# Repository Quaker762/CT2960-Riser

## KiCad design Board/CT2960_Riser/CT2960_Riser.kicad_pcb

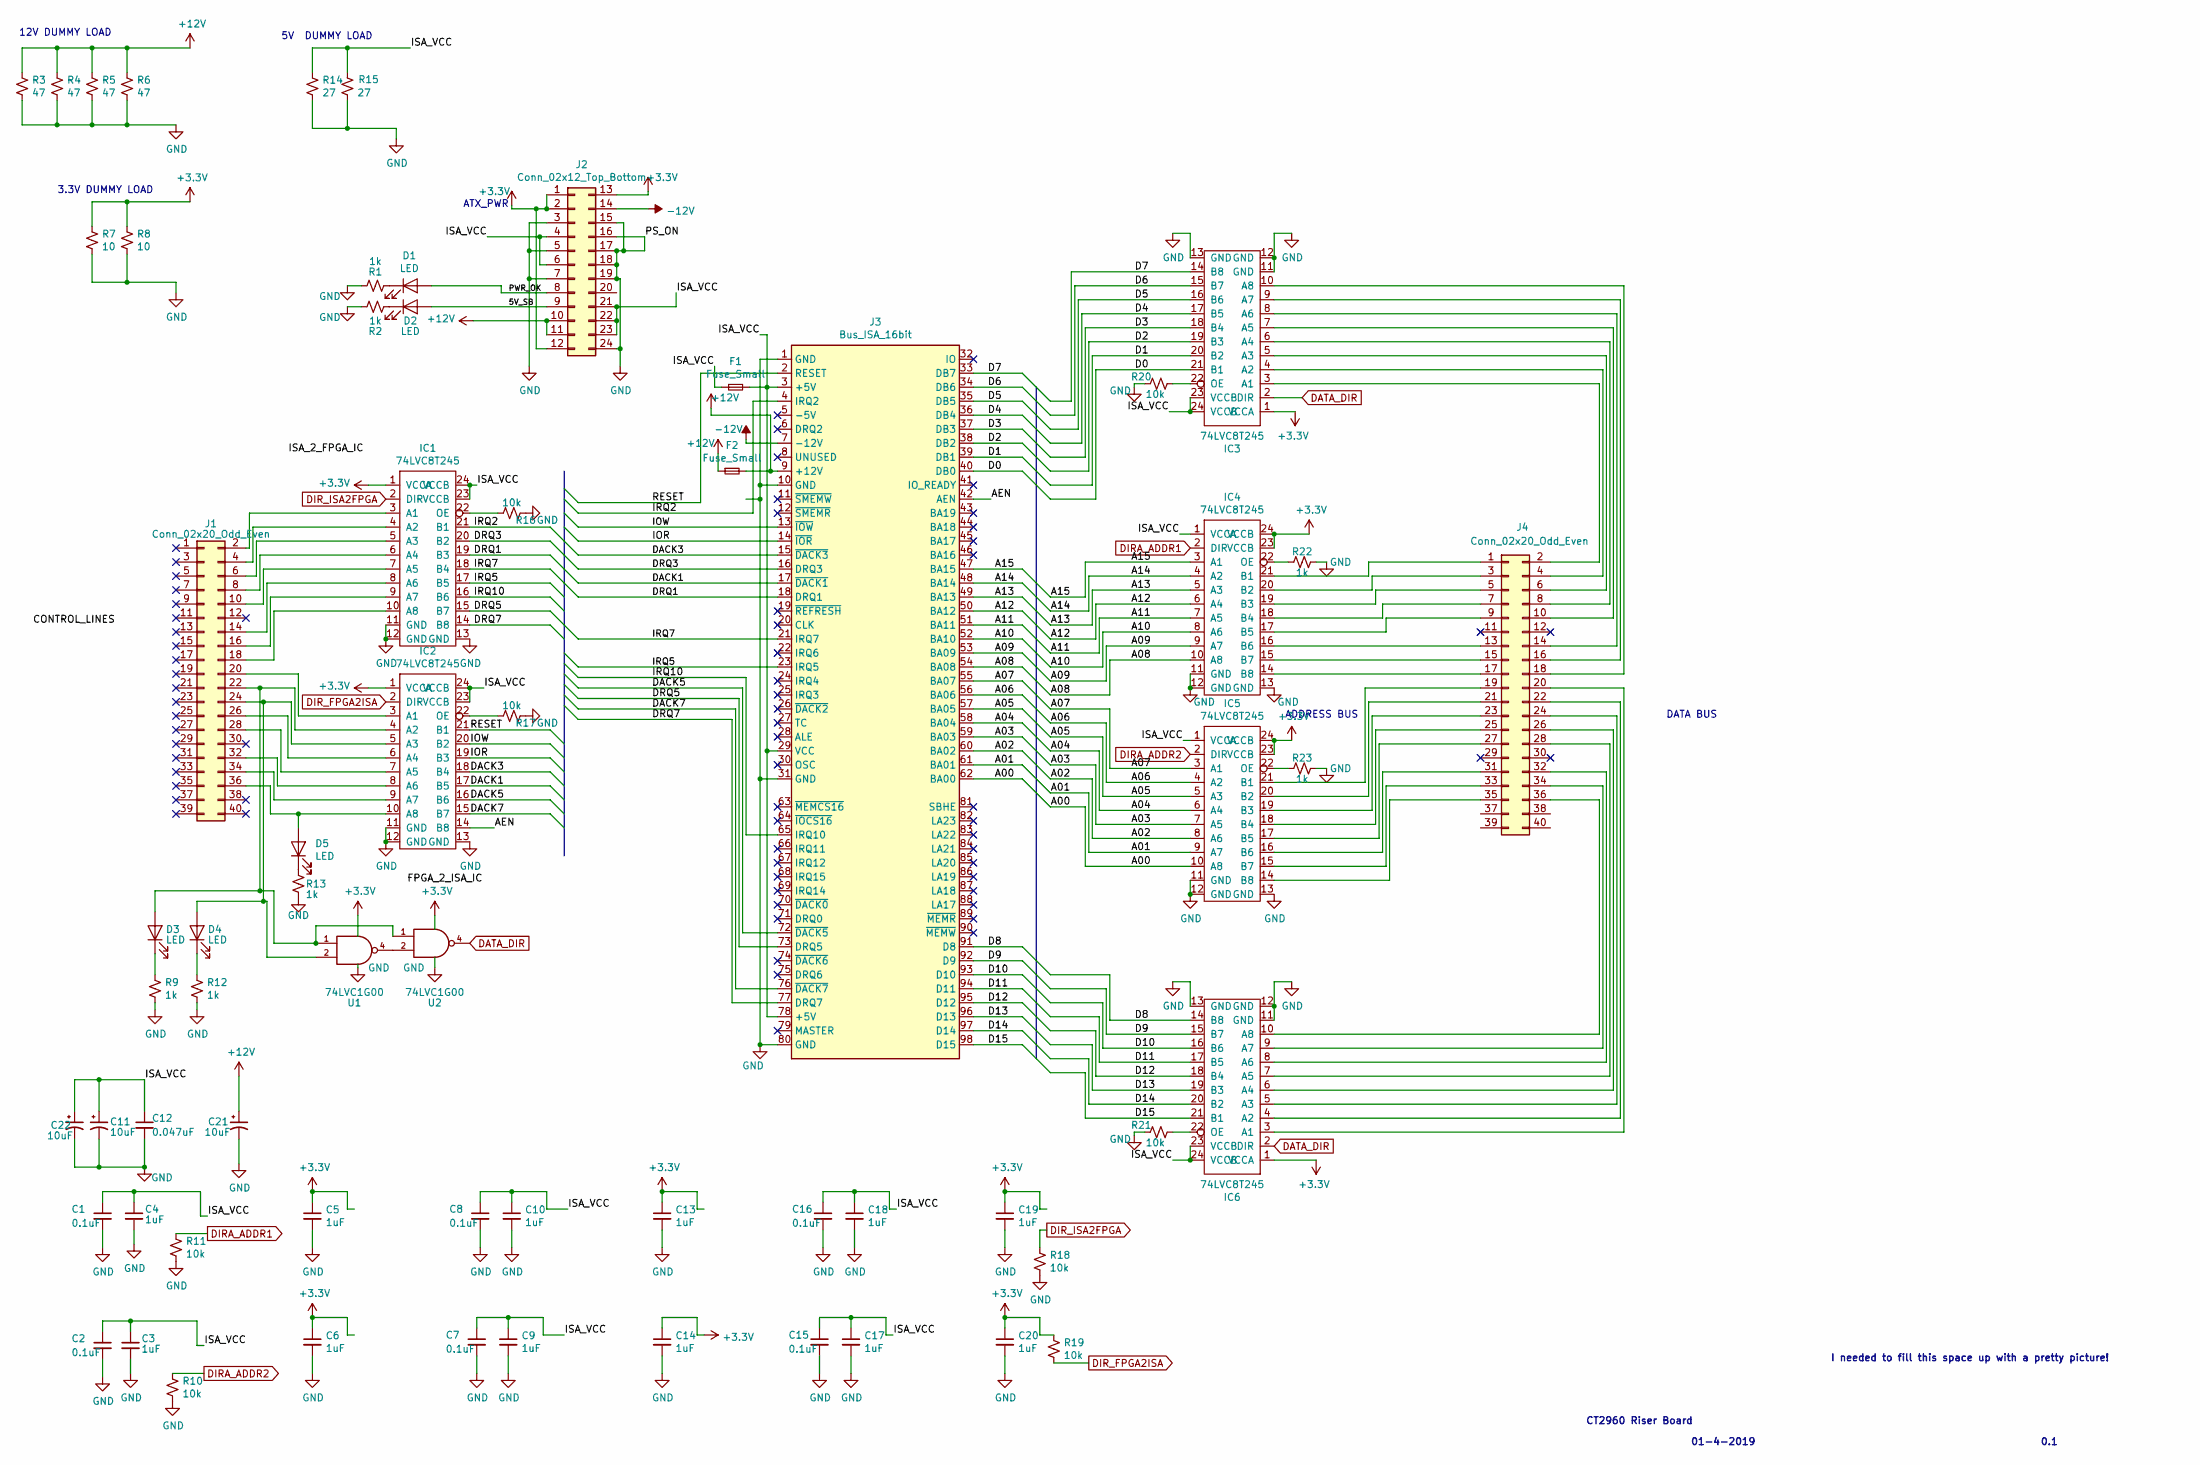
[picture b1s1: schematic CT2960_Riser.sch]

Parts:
C1, C2, C7, C8, C15, C16: 0.1uF; C_1206_3216Metric_Pad1.42x1.75mm_HandSolder
C3, C4, C5, C6, C9, C10, C13, C14, C17, C18, C19, C20: 1uF; C_1206_3216Metric_Pad1.42x1.75mm_HandSolder
C11, C21, C22: 10uF; CP_Elec_4x5.4
C12: 0.047uF; C_1206_3216Metric_Pad1.42x1.75mm_HandSolder
D1, D2, D3, D4, D5: LED; LED_1206_3216Metric
F1, F2: Fuse_Small; Fuse_1206_3216Metric_Pad1.42x1.75mm_HandSolder
IC1, IC2, IC3, IC4, IC5, IC6: 74LVC8T245; SSOP-24_3.9x8.7mm_P0.635mm
J1, J4: Conn_02x20_Odd_Even; PinSocket_2x20_P2.54mm_Vertical
J2: Conn_02x12_Top_Bottom; Molex_Mini-Fit_Jr_5566-24A_2x12_P4.20mm_Vertical
J3: Bus_ISA_16bit; ISA_Slot_98
R1, R2, R9, R12, R13, R22, R23: 1k; R_1206_3216Metric_Pad1.42x1.75mm_HandSolder
R3, R4, R5, R6: 47; RES_SMW52R0JT
R7, R8: 10; RES_SMW52R0JT
R10, R11, R16, R17, R18, R19, R20, R21: 10k; R_1206_3216Metric_Pad1.42x1.75mm_HandSolder
R14, R15: 27; RES_SMW52R0JT
U1, U2: 74LVC1G00; SOT-23-5_HandSoldering

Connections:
+3V3: C5.1, C6.1, C13.1, C14.1, C19.1, C20.1, IC1.1 (VCCA), IC2.1 (VCCA), IC3.1 (VCCA), IC4.23 (VCCB), IC4.24 (VCCB), IC5.23 (VCCB), IC5.24 (VCCB), IC6.1 (VCCA), J2.1, J2.2, J2.12, J2.13, R7.1, R8.1, R19.1, U1.5 (VCC), U2.5 (VCC)
+12V: C21.1, F2.1, F2.2, J2.10, J2.11, J3.9 (+12V), R3.1, R4.1, R5.1, R6.1
-12V: J2.14, J3.7 (-12V)
/5V_SB: D2.2 (A), J2.9
/A00: IC5.10 (A8), J3.62 (BA00)
/A01: IC5.9 (A7), J3.61 (BA01)
/A02: IC5.8 (A6), J3.60 (BA02)
/A03: IC5.7 (A5), J3.59 (BA03)
/A04: IC5.6 (A4), J3.58 (BA04)
/A05: IC5.5 (A3), J3.57 (BA05)
/A06: IC5.4 (A2), J3.56 (BA06)
/A07: IC5.3 (A1), J3.55 (BA07)
/A08: IC4.10 (A8), J3.54 (BA08)
/A09: IC4.9 (A7), J3.53 (BA09)
/A10: IC4.8 (A6), J3.52 (BA10)
/A11: IC4.7 (A5), J3.51 (BA11)
/A12: IC4.6 (A4), J3.50 (BA12)
/A13: IC4.5 (A3), J3.49 (BA13)
/A14: IC4.4 (A2), J3.48 (BA14)
/A15: IC4.3 (A1), J3.47 (BA15)
/AEN: IC2.14 (B8), J3.42 (AEN)
/D0: IC3.21 (B1), J3.40 (DB0)
/D1: IC3.20 (B2), J3.39 (DB1)
/D2: IC3.19 (B3), J3.38 (DB2)
/D3: IC3.18 (B4), J3.37 (DB3)
/D4: IC3.17 (B5), J3.36 (DB4)
/D5: IC3.16 (B6), J3.35 (DB5)
/D6: IC3.15 (B7), J3.34 (DB6)
/D7: IC3.14 (B8), J3.33 (DB7)
/D8: IC6.14 (B8), J3.91 (D8)
/D9: IC6.15 (B7), J3.92 (D9)
/D10: IC6.16 (B6), J3.93 (D10)
/D11: IC6.17 (B5), J3.94 (D11)
/D12: IC6.18 (B4), J3.95 (D12)
/D13: IC6.19 (B3), J3.96 (D13)
/D14: IC6.20 (B2), J3.97 (D14)
/D15: IC6.21 (B1), J3.98 (D15)
/DACK1: IC2.17 (B5), J3.17 (~DACK1)
/DACK3: IC2.18 (B4), J3.15 (~DACK3)
/DACK5: IC2.16 (B6), J3.72 (~DACK5)
/DACK7: IC2.15 (B7), J3.76 (~DACK7)
/DRQ1: IC1.19 (B3), J3.18 (DRQ1)
/DRQ3: IC1.20 (B2), J3.16 (DRQ3)
/DRQ5: IC1.15 (B7), J3.73 (DRQ5)
/DRQ7: IC1.14 (B8), J3.77 (DRQ7)
/IOR: IC2.19 (B3), J3.14 (~IOR); also elsewhere on the board
/IOW: IC2.20 (B2), J3.13 (~IOW); also elsewhere on the board
/IRQ2: IC1.21 (B1), J3.4 (IRQ2)
/IRQ5: IC1.17 (B5), J3.23 (IRQ5)
/IRQ7: IC1.18 (B4), J3.21 (IRQ7)
/IRQ10: IC1.16 (B6), J3.65 (IRQ10)
/ISA_VCC: C1.1, C2.1, C3.1, C4.1, C7.1, C8.1, C9.1, C10.1, C11.1, C12.1, C15.1, C16.1, C17.1, C18.1, C22.1, F1.1, F1.2, IC1.23 (VCCB), IC1.24 (VCCB), IC2.23 (VCCB), IC2.24 (VCCB), IC3.23 (VCCB), IC3.24 (VCCB), IC4.1 (VCCA), IC5.1 (VCCA), IC6.23 (VCCB), IC6.24 (VCCB), J2.4, J2.6, J2.21, J2.22, J2.23, J3.3 (+5V), J3.29 (VCC), J3.78 (+5V), R14.1, R15.1
/PWR_OK: D1.2 (A), J2.8
/RESET: IC2.21 (B1), J3.2 (RESET)
DATA_DIR: IC3.2 (DIR), IC6.2 (DIR), U2.4
DIRA_ADDR1: IC4.2 (DIR), R11.1
DIRA_ADDR2: IC5.2 (DIR), R10.1
DIR_FPGA2ISA: IC2.2 (DIR), R19.2
DIR_ISA2FPGA: IC1.2 (DIR), R18.1
GND: C1.2, C2.2, C3.2, C4.2, C5.2, C6.2, C7.2, C8.2, C9.2, C10.2, C11.2, C12.2, C13.2, C14.2, C15.2, C16.2, C17.2, C18.2, C19.2, C20.2, C21.2, C22.2, IC1.11 (GND), IC1.12 (GND), IC1.13 (GND), IC2.11 (GND), IC2.12 (GND), IC2.13 (GND), IC3.11 (GND), IC3.12 (GND), IC3.13 (GND), IC4.11 (GND), IC4.12 (GND), IC4.13 (GND), IC5.11 (GND), IC5.12 (GND), IC5.13 (GND), IC6.11 (GND), IC6.12 (GND), IC6.13 (GND), J2.3, J2.5, J2.7, J2.15, J2.16, J2.17, J2.18, J2.19, J2.24, J3.1 (GND), J3.10 (GND), J3.31 (GND), J3.80 (GND), R1.2, R2.1, R3.2, R4.2, R5.2, R6.2, R7.2, R8.2, R9.2, R10.2, R11.2, R12.2, R13.2, R14.2, R15.2, R16.2, R17.2, R18.2, R20.2, R21.2, R22.1, R23.1, U1.3 (GND), U2.3 (GND)
unnamed: D1.1 (K), R1.1
unnamed: D2.1 (K), R2.2
unnamed 62: D3.1 (K), R9.1; also elsewhere on the board
unnamed 63: D4.1 (K), R12.1; also elsewhere on the board
unnamed: D5.1 (K), R13.1
unnamed: D5.2 (A), IC2.10 (A8), J1.36
unnamed: IC1.3 (A1), J1.2
unnamed: IC1.4 (A2), J1.4
unnamed: IC1.5 (A3), J1.6
unnamed: IC1.6 (A4), J1.8
unnamed: IC1.7 (A5), J1.10
unnamed: IC1.8 (A6), J1.14
unnamed: IC1.9 (A7), J1.16
unnamed: IC1.10 (A8), J1.18
unnamed: IC1.22 (OE), R16.1
unnamed: IC2.3 (A1), J1.20
unnamed: D3.2 (A), IC2.4 (A2), J1.22, U1.1, U2.1
unnamed: D4.2 (A), IC2.5 (A3), J1.24, U1.2
unnamed: IC2.6 (A4), J1.26
unnamed: IC2.7 (A5), J1.28
unnamed: IC2.8 (A6), J1.32
unnamed: IC2.9 (A7), J1.34
unnamed: IC2.22 (OE), R17.1
unnamed: IC3.3 (A1), J4.2
unnamed: IC3.4 (A2), J4.4
unnamed: IC3.5 (A3), J4.6
unnamed: IC3.6 (A4), J4.8
unnamed: IC3.7 (A5), J4.10
unnamed: IC3.8 (A6), J4.14
unnamed: IC3.9 (A7), J4.16
unnamed: IC3.10 (A8), J4.18
unnamed: IC3.22 (OE), R20.1
unnamed: IC4.14 (B8), J4.17
unnamed: IC4.15 (B7), J4.15
unnamed: IC4.16 (B6), J4.13
unnamed: IC4.17 (B5), J4.9
unnamed: IC4.18 (B4), J4.7
unnamed: IC4.19 (B3), J4.5
unnamed: IC4.20 (B2), J4.3
unnamed: IC4.21 (B1), J4.1
unnamed: IC4.22 (OE), R22.2
unnamed: IC5.14 (B8), J4.35
unnamed: IC5.15 (B7), J4.33
unnamed: IC5.16 (B6), J4.31
unnamed: IC5.17 (B5), J4.27
unnamed: IC5.18 (B4), J4.25
unnamed: IC5.19 (B3), J4.23
unnamed: IC5.20 (B2), J4.21
unnamed: IC5.21 (B1), J4.19
unnamed: IC5.22 (OE), R23.2
unnamed: IC6.3 (A1), J4.20
unnamed: IC6.4 (A2), J4.22
unnamed: IC6.5 (A3), J4.24
unnamed: IC6.6 (A4), J4.26
unnamed: IC6.7 (A5), J4.28
unnamed: IC6.8 (A6), J4.32
unnamed: IC6.9 (A7), J4.34
unnamed: IC6.10 (A8), J4.36
unnamed: IC6.22 (OE), R21.1
unnamed: U1.4, U2.2

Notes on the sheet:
CT2960 Riser Board
0.1
01-4-2019
ADDRESS BUS
ATX_PWR
12V DUMMY LOAD
DATA BUS
I needed to fill this space up with a pretty picture!
3.3V DUMMY LOAD
5V DUMMY LOAD

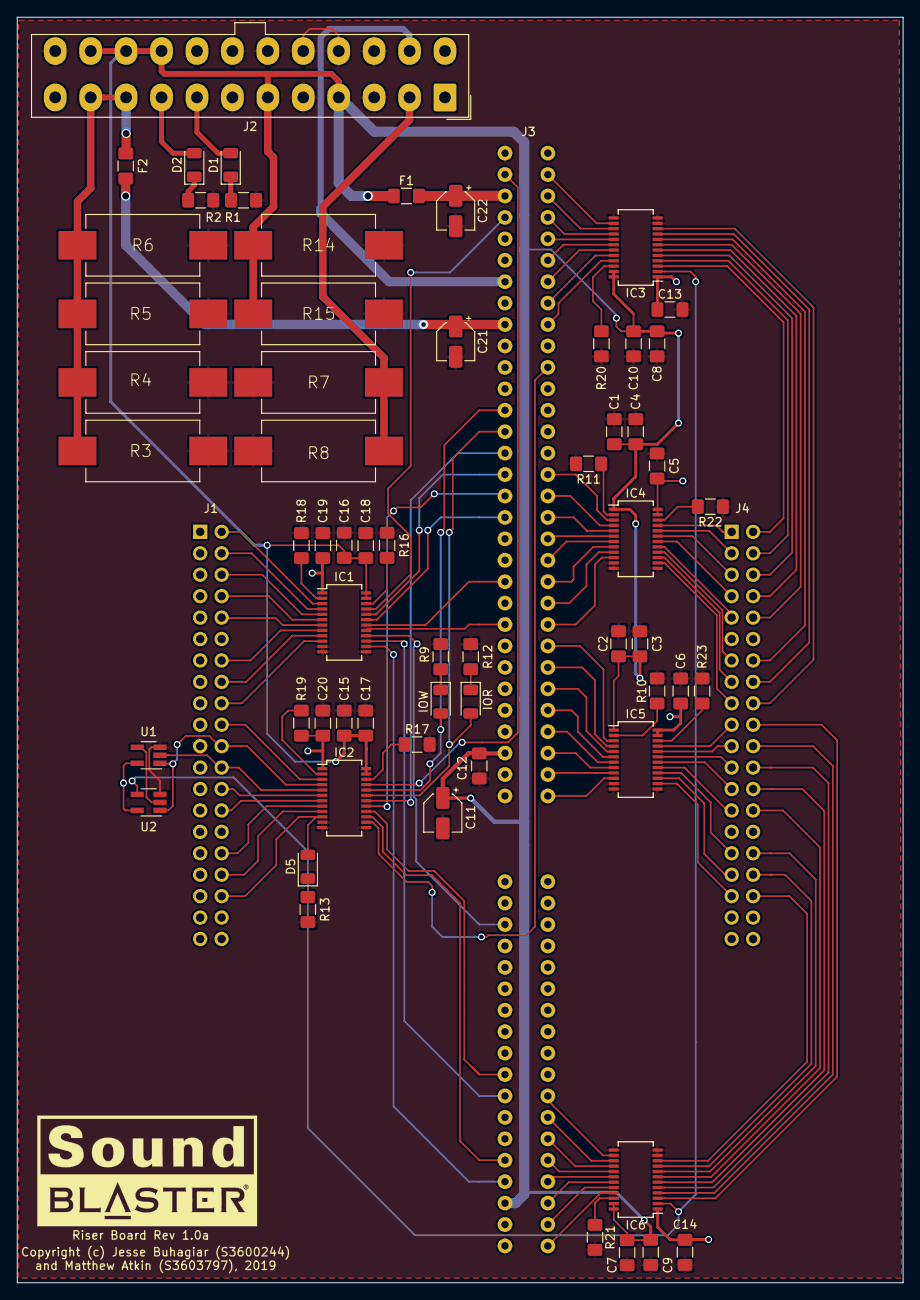
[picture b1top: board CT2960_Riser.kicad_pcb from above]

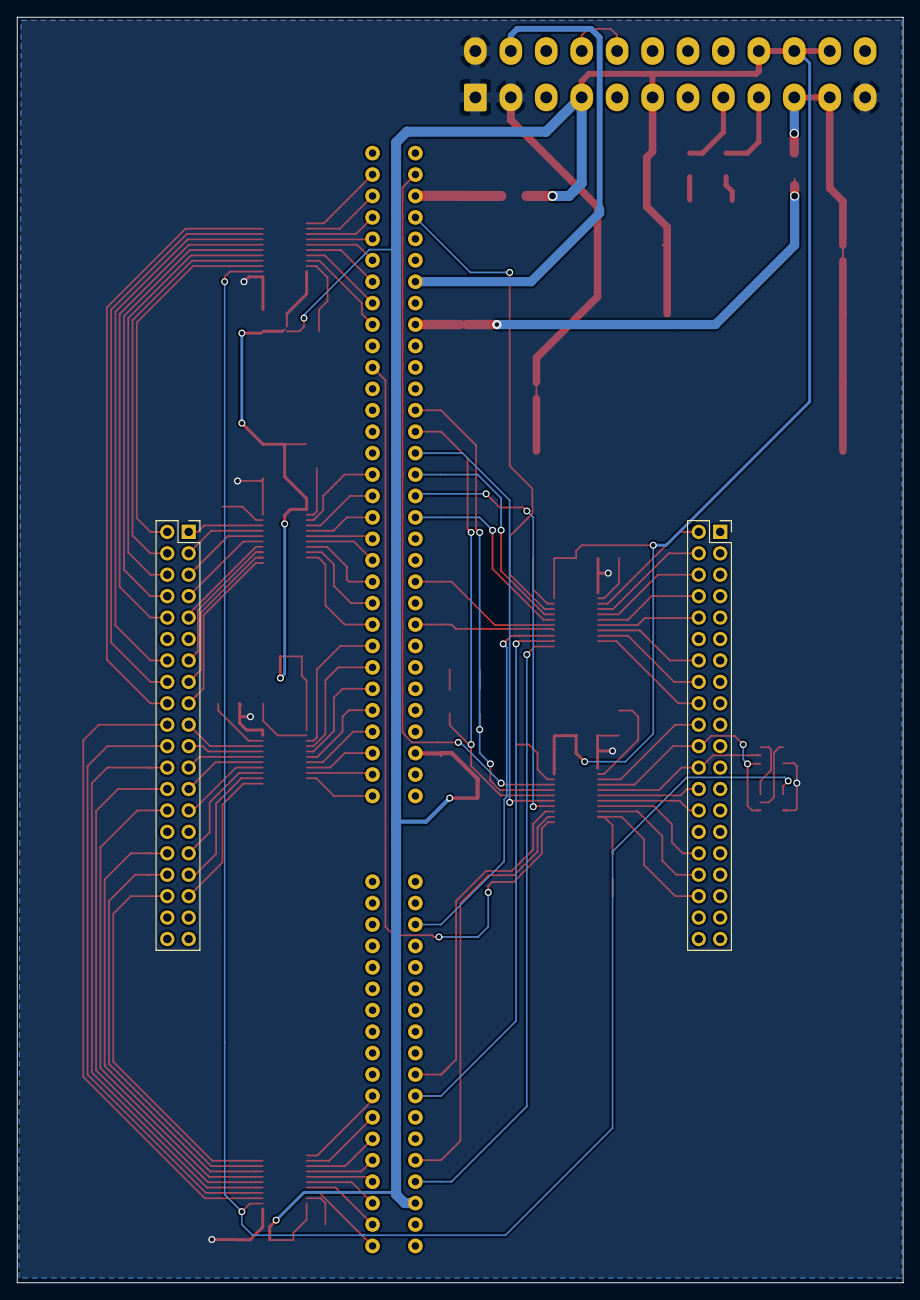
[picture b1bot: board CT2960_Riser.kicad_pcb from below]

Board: 2 copper layers, 105.0 x 150.0 mm, 64 parts (2 on the bottom side), 120 nets.

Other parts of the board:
IOR: LED; LED_1206_3216Metric
IOW: LED; LED_1206_3216Metric

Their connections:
/IOR: IOR.2; also elsewhere on the board
/IOW: IOW.2; also elsewhere on the board
unnamed 62: IOW.1; also elsewhere on the board
unnamed 63: IOR.1; also elsewhere on the board

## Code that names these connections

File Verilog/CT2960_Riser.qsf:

# -------------------------------------------------------------------------- #
#
# Copyright (C) 2018  Intel Corporation. All rights reserved.
# Your use of Intel Corporation's design tools, logic functions 
# and other software and tools, and its AMPP partner logic 
# functions, and any output files from any of the foregoing 
# (including device programming or simulation files), and any 
# associated documentation or information are expressly subject 
# to the terms and conditions of the Intel Program License 
# Subscription Agreement, the Intel Quartus Prime License Agreement,
# the Intel FPGA IP License Agreement, or other applicable license
# agreement, including, without limitation, that your use is for
# the sole purpose of programming logic devices manufactured by
# Intel and sold by Intel or its authorized distributors.  Please
# refer to the applicable agreement for further details.
#
# -------------------------------------------------------------------------- #
#
# Quartus Prime
# Version 18.1.0 Build 625 09/12/2018 SJ Lite Edition
# Date created = 17:53:00  May 14, 2019
#
# -------------------------------------------------------------------------- #
#
# Notes:
#
# 1) The default values for assignments are stored in the file:
#		CT2960_Riser_assignment_defaults.qdf
#    If this file doesn't exist, see file:
#		assignment_defaults.qdf
#
# 2) Altera recommends that you do not modify this file. This
#    file is updated automatically by the Quartus Prime software
#    and any changes you make may be lost or overwritten.
#
# -------------------------------------------------------------------------- #


set_global_assignment -name FAMILY "Cyclone V"
set_global_assignment -name DEVICE 5CSEBA6U23I7DK
set_global_assignment -name TOP_LEVEL_ENTITY SuperIO
set_global_assignment -name ORIGINAL_QUARTUS_VERSION 18.1.0
set_global_assignment -name PROJECT_CREATION_TIME_DATE "17:53:00  MAY 14, 2019"
set_global_assignment -name LAST_QUARTUS_VERSION "18.1.0 Lite Edition"
set_global_assignment -name PROJECT_OUTPUT_DIRECTORY output_files
set_global_assignment -name MIN_CORE_JUNCTION_TEMP "-40"
set_global_assignment -name MAX_CORE_JUNCTION_TEMP 100
set_global_assignment -name ERROR_CHECK_FREQUENCY_DIVISOR 256
set_location_assignment PIN_V12 -to A[15]
set_location_assignment PIN_W12 -to A[14]
set_location_assignment PIN_D8 -to A[13]
set_location_assignment PIN_AF7 -to A[12]
set_location_assignment PIN_AF4 -to A[11]
set_location_assignment PIN_AD5 -to A[10]
set_location_assignment PIN_AE23 -to A[9]
set_location_assignment PIN_AD23 -to A[8]
set_location_assignment PIN_D12 -to A[7]
set_location_assignment PIN_C12 -to A[6]
set_location_assignment PIN_AC23 -to A[5]
set_location_assignment PIN_Y19 -to A[4]
set_location_assignment PIN_AA19 -to A[3]
set_location_assignment PIN_AA18 -to A[2]
set_location_assignment PIN_Y18 -to A[1]
set_location_assignment PIN_AB25 -to A[0]
set_location_assignment PIN_E8 -to D[0]
set_location_assignment PIN_D11 -to D[1]
set_location_assignment PIN_AH13 -to D[2]
set_location_assignment PIN_AH14 -to D[3]
set_location_assignment PIN_AH3 -to D[4]
set_location_assignment PIN_AG14 -to D[5]
set_location_assignment PIN_AE6 -to D[6]
set_location_assignment PIN_AE24 -to D[7]
set_location_assignment PIN_AD20 -to D[15]
set_location_assignment PIN_AD17 -to D[14]
set_location_assignment PIN_AC22 -to D[13]
set_location_assignment PIN_AB23 -to D[12]
set_location_assignment PIN_W11 -to D[11]
set_location_assignment PIN_W14 -to D[10]
set_location_assignment PIN_Y17 -to D[9]
set_location_assignment PIN_AB26 -to D[8]
set_location_assignment PIN_AE19 -to IRQ2
set_location_assignment PIN_AG15 -to DRQ3
set_location_assignment PIN_AF18 -to DRQ1
set_location_assignment PIN_AG18 -to IRQ7
set_location_assignment PIN_AG19 -to IRQ5
set_location_assignment PIN_AG20 -to IRQ10
set_location_assignment PIN_AF22 -to DRQ5
set_location_assignment PIN_AH23 -to DRQ7
set_location_assignment PIN_AH21 -to RESET
set_location_assignment PIN_AG24 -to IOW
set_location_assignment PIN_AG23 -to IOR
set_location_assignment PIN_AH24 -to DACK3
set_location_assignment PIN_AG25 -to DACK1
set_location_assignment PIN_AG26 -to DACK5
set_location_assignment PIN_AE25 -to DACK7
set_location_assignment PIN_AG28 -to AEN
set_global_assignment -name POWER_PRESET_COOLING_SOLUTION "23 MM HEAT SINK WITH 200 LFPM AIRFLOW"
set_global_assignment -name POWER_BOARD_THERMAL_MODEL "NONE (CONSERVATIVE)"
set_location_assignment PIN_V11 -to clk_50MHz
set_global_assignment -name PARTITION_NETLIST_TYPE SOURCE -section_id Top
set_global_assignment -name PARTITION_FITTER_PRESERVATION_LEVEL PLACEMENT_AND_ROUTING -section_id Top
set_global_assignment -name PARTITION_COLOR 16764057 -section_id Top
set_instance_assignment -name IO_STANDARD "3.3-V LVTTL" -to A[15]
set_instance_assignment -name IO_STANDARD "3.3-V LVTTL" -to A[14]
set_instance_assignment -name IO_STANDARD "3.3-V LVTTL" -to A[13]
set_instance_assignment -name IO_STANDARD "3.3-V LVTTL" -to A[12]
set_instance_assignment -name IO_STANDARD "3.3-V LVTTL" -to A[11]
set_instance_assignment -name IO_STANDARD "3.3-V LVTTL" -to A[10]
set_instance_assignment -name IO_STANDARD "3.3-V LVTTL" -to A[9]
set_instance_assignment -name IO_STANDARD "3.3-V LVTTL" -to A[8]
set_instance_assignment -name IO_STANDARD "3.3-V LVTTL" -to A[7]
set_instance_assignment -name IO_STANDARD "3.3-V LVTTL" -to A[6]
set_instance_assignment -name IO_STANDARD "3.3-V LVTTL" -to A[5]
set_instance_assignment -name IO_STANDARD "3.3-V LVTTL" -to A[4]
set_instance_assignment -name IO_STANDARD "3.3-V LVTTL" -to A[3]
set_instance_assignment -name IO_STANDARD "3.3-V LVTTL" -to A[2]
set_instance_assignment -name IO_STANDARD "3.3-V LVTTL" -to A[1]
set_instance_assignment -name IO_STANDARD "3.3-V LVTTL" -to A[0]
set_instance_assignment -name IO_STANDARD "3.3-V LVTTL" -to D[15]
set_instance_assignment -name IO_STANDARD "3.3-V LVTTL" -to D[14]
set_instance_assignment -name IO_STANDARD "3.3-V LVTTL" -to D[13]
set_instance_assignment -name IO_STANDARD "3.3-V LVTTL" -to D[12]
set_instance_assignment -name IO_STANDARD "3.3-V LVTTL" -to D[11]
set_instance_assignment -name IO_STANDARD "3.3-V LVTTL" -to D[10]
set_instance_assignment -name IO_STANDARD "3.3-V LVTTL" -to D[9]
set_instance_assignment -name IO_STANDARD "3.3-V LVTTL" -to D[8]
set_instance_assignment -name IO_STANDARD "3.3-V LVTTL" -to D[7]
set_instance_assignment -name IO_STANDARD "3.3-V LVTTL" -to D[6]
set_instance_assignment -name IO_STANDARD "3.3-V LVTTL" -to D[5]
set_instance_assignment -name IO_STANDARD "3.3-V LVTTL" -to D[4]
set_instance_assignment -name IO_STANDARD "3.3-V LVTTL" -to D[3]
set_instance_assignment -name IO_STANDARD "3.3-V LVTTL" -to D[2]
set_instance_assignment -name IO_STANDARD "3.3-V LVTTL" -to D[1]
set_instance_assignment -name IO_STANDARD "3.3-V LVTTL" -to D[0]
set_instance_assignment -name IO_STANDARD "3.3-V LVTTL" -to DACK1
set_instance_assignment -name IO_STANDARD "3.3-V LVTTL" -to DACK3
set_instance_assignment -name IO_STANDARD "3.3-V LVTTL" -to DACK5
set_instance_assignment -name IO_STANDARD "3.3-V LVTTL" -to DACK7
set_instance_assignment -name IO_STANDARD "3.3-V LVTTL" -to DRQ1
set_instance_assignment -name IO_STANDARD "3.3-V LVTTL" -to DRQ3
set_instance_assignment -name IO_STANDARD "3.3-V LVTTL" -to DRQ5
set_instance_assignment -name IO_STANDARD "3.3-V LVTTL" -to DRQ7
set_instance_assignment -name IO_STANDARD "3.3-V LVTTL" -to IOR
set_instance_assignment -name IO_STANDARD "3.3-V LVTTL" -to IOW
set_instance_assignment -name IO_STANDARD "3.3-V LVTTL" -to IRQ2
set_instance_assignment -name IO_STANDARD "3.3-V LVTTL" -to IRQ5
set_instance_assignment -name IO_STANDARD "3.3-V LVTTL" -to IRQ7
set_instance_assignment -name IO_STANDARD "3.3-V LVTTL" -to IRQ10
set_instance_assignment -name IO_STANDARD "3.3-V LVTTL" -to RESET
set_instance_assignment -name IO_STANDARD "3.3-V LVTTL" -to AEN
set_instance_assignment -name IO_STANDARD "3.3-V LVTTL" -to clk_50MHz
set_global_assignment -name VERILOG_FILE src/Verilog/Bus_Interface.v
set_global_assignment -name VERILOG_FILE src/Verilog/State_Machine.v
set_global_assignment -name VERILOG_FILE src/Verilog/Register.v
set_global_assignment -name VERILOG_FILE src/Verilog/Register_File.v
set_global_assignment -name VERILOG_FILE src/Verilog/SuperIO.v
set_global_assignment -name QIP_FILE src/Verilog/ip/Bus_Clock_8MHz.qip
set_global_assignment -name SIP_FILE src/Verilog/ip/Bus_Clock_8MHz.sip
set_global_assignment -name VERILOG_FILE src/Verilog/Address_Decoder.v
set_global_assignment -name VERILOG_FILE src/Verilog/Mux_4_To_1.v
set_global_assignment -name VERILOG_FILE src/Verilog/RegisterRW.v
set_location_assignment PIN_AH17 -to global_reset
set_instance_assignment -name IO_STANDARD "3.3-V LVTTL" -to global_reset
set_instance_assignment -name PARTITION_HIERARCHY root_partition -to | -section_id Top

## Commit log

2019-04-27 Fixed DRC from reporting unconnected trace/pad
2019-04-28 Fixed up pin header location
    It was off by a good 2mm... Fantastic for if you want to have it NOT fit
    on top of the DE10....
2019-05-06 Commit 06052019
2019-05-14 Fixes
2019-05-15 Basic Verilog skeleton and attempt at reset state machine
2019-05-15 Added tcl script and re organised directories
2019-05-15 Updates gitignore to allow tcl files and added basic test
2019-05-19 Created the port scanner system, allowing us to check which base address the reset port is sitting on
2019-05-20 Minor adjustment
2019-05-20 Independant bus clock
2019-05-20 Slight change
2019-05-20 Set back to only reset on port 220
2019-05-23 Implemented some TLE stuff
2019-05-23 New design coming along
2019-05-23 tabs to spaces
2019-05-23 Tidy up and change to read from the bus directly to the regfile rather than to the buffer first
2019-05-23 Elaborated register file
    Register file has now been implemented, however it is currently unwired.
2019-05-25 Done afaik
2019-05-25 Hopefully done
2019-05-28 Masked read bits
2019-05-28 revert
2019-05-28 Fuck QSYS
2019-05-29 Qsys almost there
2019-05-29 Works lmao
2019-05-31 tcl timing
2019-06-01 sad yeet
2019-06-01 asdf
2019-06-01 clk out
2019-06-01 yeet
2019-06-03 new write
2019-06-03 Clock is now 6MHz
2019-06-03 Added card reset
2019-06-05 More tcl scripts for simulation
2019-06-05 Add C driver
2019-06-05 Missed a file whoops
2019-06-05 yikes

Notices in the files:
Board/CT2960_Riser/CT2960_Riser.kicad_pcb:
Copyright (c) Jesse Buhagiar (S3600244)
